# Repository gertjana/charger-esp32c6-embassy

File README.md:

# ESP32-C6 Embassy Charged

An ESP32-C6 based electric vehicle charging station built with Embassy async runtime and OCPP 1.6 support.

## Quick Start

### 1. Configuration Setup

Copy the example configuration file and update it with your settings:

```bash
cp app_config.toml.example app_config.toml
```

Edit `app_config.toml` with your actual values:

```toml
[wifi]
ssid = "YOUR_WIFI_NETWORK"
password = "YOUR_WIFI_PASSWORD"

[charger]
name = "esp32c6 charger 001"
model = "ESP32-C6"
vendor = "GA Make"
serial = "esp32c6-charger-001"

[mqtt]
broker = "broker.hivemq.com"
port = 1883
client_id = "esp32c6-charger-001"
```

### 2. Environment Variable Overrides (Optional)

You can override any configuration value using environment variables, the naming i:

```
CHARGER_<section>_key>
for instance CHARGER_WIFI_ID
```

### 3. Build and Flash

```bash
cargo build
cargo run
```

## OCPP Protocol Support

The charger implements OCPP 1.6 protocol:

### Outgoing Messages (Published to `/charger/{serial}`)
- **Authorize**: Sent when a user swipes their card for authorization
- **BootNotification**: Sent once at startup with charger model, vendor and serial details
- **Heartbeat**: Periodic status updates with configurable interval
- **StartTransaction**: Charging session initiation with ID tag and timestamp
- **StopTransaction**: Charging session completion with transaction ID and timestamp

### Responses and incoming Messages (Subscribed to `/system/{serial}`)

## Development

This project uses:
- **Embassy**: Async runtime for embedded Rust with concurrent task management
- **ESP-HAL**: Hardware abstraction for ESP32-C6
- **OCPP-RS**: Open Charge Point Protocol implementation
- **Embassy-Net**: Networking stack with WiFi and MQTT support
- **Rust-MQTT**: Lightweight MQTT client for embedded systems

### Architecture
The system is built around Embassy async tasks:
- **Network Stack**: WiFi connection management and IP configuration
- **MQTT Client**: Bidirectional message of OCPP Messages
- **NTP Client**: Queries NTP Server every 4 hours and syncing with local timer in the ESP32-C6
- **OCPP 1.6**: minimum support for OCPP 1.6 to support basic Charging behaviour
- **Hardware Tasks**: GPIO monitoring for cable detection, card swipes. Led and Relay control and update a small display
- **Periodic Tasks**: for instance Heartbeat transmission and boot notifications (once)

#### Application Diagram

#### State Diagram

### Memory Management
- **Heap Size**: 64KB allocated for dynamic memory
- **Message Buffers**: 2048-byte capacity for larger OCPP messages
- **Channel Queues**: 5-message capacity for MQTT send/receive operations
- **Static Allocation**: Embassy static cells for zero-allocation async runtime

## Security Note

The `app_config.toml` file contains sensitive information (WiFi passwords, etc.) and is excluded from version control. Always use the `.example` file as a template for new deployments.

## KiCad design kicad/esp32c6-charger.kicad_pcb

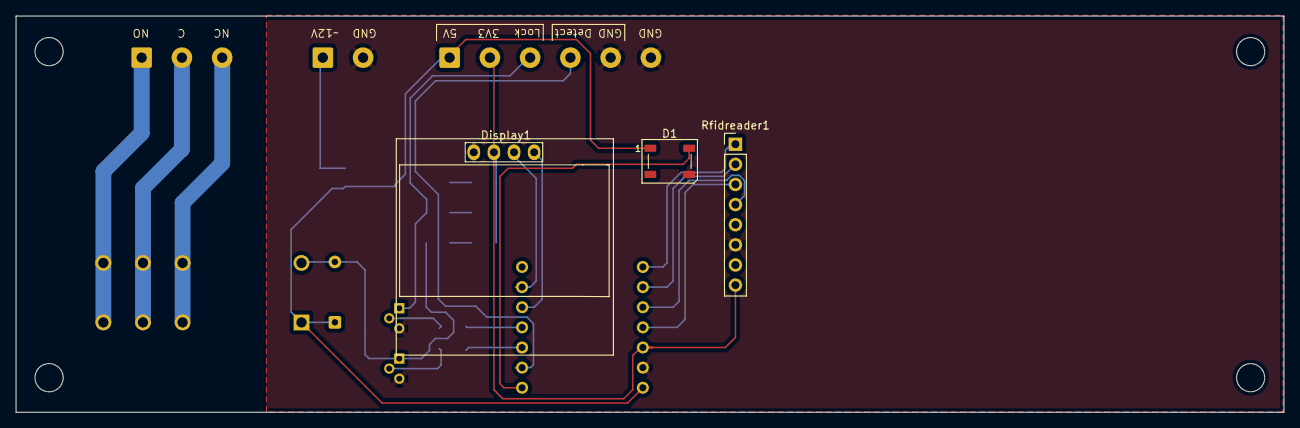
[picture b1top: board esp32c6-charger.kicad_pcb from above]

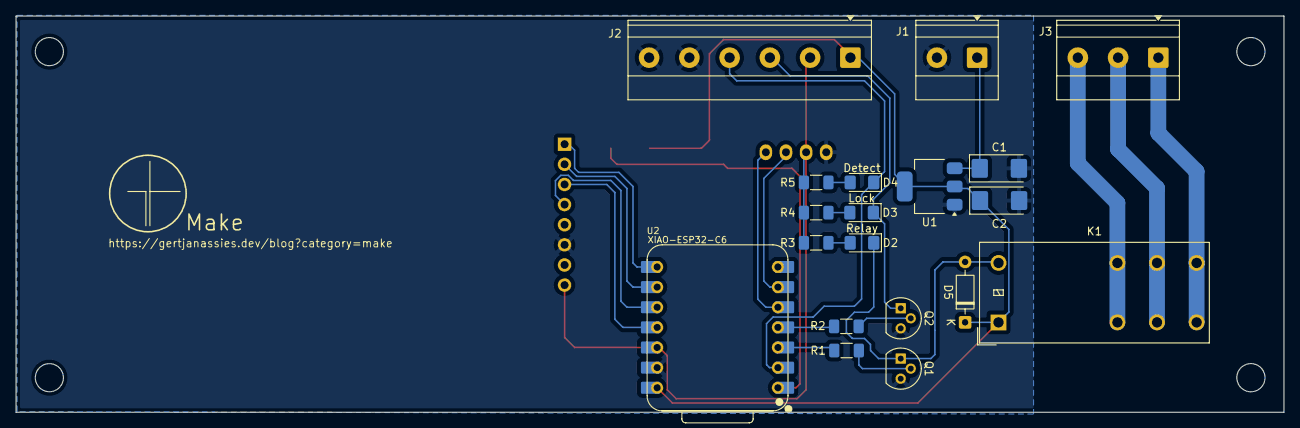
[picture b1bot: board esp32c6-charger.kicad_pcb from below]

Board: 2 copper layers, 160.0 x 50.0 mm, 22 parts (19 on the bottom side), 24 nets.

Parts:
C1: 10uF; CP_EIA-6032-28_Kemet-C
C2: 22uF; CP_EIA-6032-28_Kemet-C
D1: WS2812B; LED_WS2812B_PLCC4_5.0x5.0mm_P3.2mm
D2: Relay; LED_1206_3216Metric_Pad1.42x1.75mm_HandSolder
D3: Lock; LED_1206_3216Metric_Pad1.42x1.75mm_HandSolder
D4: Detect; LED_1206_3216Metric_Pad1.42x1.75mm_HandSolder
D5: 1N4148WS; D_DO-35_SOD27_P7.62mm_Horizontal
Display1: SSD1306; 128x64OLED
J1: Conn_01x02_Socket; TerminalBlock_Phoenix_MKDS-1,5-2-5.08_1x02_P5.08mm_Horizont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
J2: Power/Lock/Detect; TerminalBlock_Phoenix_MKDS-1,5-6-5.08_1x06_P5.08mm_Horizont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
J3: Relay; TerminalBlock_Phoenix_MKDS-1,5-3-5.08_1x03_P5.08mm_Horizont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
K1: G2RL-1; Relay_SPDT_Omron_G2RL-1-E
Q1, Q2: BC337; TO-92
R1, R2: 10k; R_1206_3216Metric_Pad1.30x1.75mm_HandSolder
R3, R4, R5: 68Ω; R_1206_3216Metric_Pad1.30x1.75mm_HandSolder
Rfidreader1: RC522
U1: AMS1117-5.0; SOT-223-3_TabPin2
U2: XIAO-ESP32-C6; XIAO-ESP32C6-DIP

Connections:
+12V: C1.1, J1.1, U1.3 (VI)
/CS: Rfidreader1.1 (SDA), U2.8 (GPIO17/D7/RX)
/Detect: D4.1 (K), J2.4, U2.2 (GPIO1/A1/D1)
/LED: D1.4 (DIN), U2.1 (GPIO0/A0/D0)
/Lock: D3.1 (K), J2.3, Q2.1 (C)
/MISO: Rfidreader1.4 (MISO), U2.10 (GPIO20/D9/MISO)
/MOSI: Rfidreader1.3 (MOSI), U2.11 (GPIO18/D10/MOSI)
/Relay: D2.1 (K), D5.2 (A), K1.A2, Q1.1 (C)
/SCK: Rfidreader1.2 (SCK), U2.9 (GPIO19/D8/SCK)
/SCL: Display1.3 (SCL), U2.6 (GPIO23/D5/SCL)
/SDA: Display1.4 (SDA), U2.5 (GPIO22/D4/SDA)
GND: C1.2, C2.2, D1.3 (VSS), Display1.1 (GND), J1.2, J2.5, J2.6, Q1.3 (E), Q2.3 (E), Rfidreader1.6 (GND), U1.1 (GND), U2.13 (GND)
unnamed: D2.2 (A), R3.1
unnamed: D3.2 (A), R4.1
unnamed: D4.2 (A), R5.1
unnamed: J3.1, K1.14
unnamed: J3.2, K1.11
unnamed: J3.3, K1.12
unnamed: Q1.2 (B), R1.2
unnamed: Q2.2 (B), R2.2
unnamed: R1.1, U2.3 (GPIO2/A2/D2)
unnamed: R2.1, U2.4 (GPIO21/D3)
VCC: Display1.2 (VCC), J2.2, R3.2, R4.2, R5.2, Rfidreader1.8 (3,3V), U2.12 (3V3)
VDD: C2.1, D1.1 (VDD), D5.1 (K), J2.1, K1.A1, U1.2 (VO), U2.14 (VBUS)

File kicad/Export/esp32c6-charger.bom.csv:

"Id";"Designator";"Footprint";"Quantity";"Designation";"Supplier and ref";
1;"Display1";"128x64OLED";1;"SSD1306";;;
2;"Rfidreader1";"RC522";1;"RC522";;;
3;"D1";"LED_WS2812B_PLCC4_5.0x5.0mm_P3.2mm";1;"WS2812B";;;
4;"U2";"XIAO-ESP32C6-DIP";1;"XIAO-ESP32-C6";;;
5;"D4";"LED_1206_3216Metric_Pad1.42x1.75mm_HandSolder";1;"Detect";;;
6;"D3";"LED_1206_3216Metric_Pad1.42x1.75mm_HandSolder";1;"Lock";;;
7;"R3,R4,R5";"R_1206_3216Metric_Pad1.30x1.75mm_HandSolder";3;"68Ω";;;
8;"D2";"LED_1206_3216Metric_Pad1.42x1.75mm_HandSolder";1;"Relay";;;
9;"Q2,Q1";"TO-92";2;"BC337";;;
10;"J1";"TerminalBlock_Phoenix_MKDS-1,5-2-5.08_1x02_P5.08mm_Horizontal";1;"Conn_01x02_Socket";;;
11;"C1";"CP_EIA-6032-28_Kemet-C";1;"10uF";;;
12;"R1,R2";"R_1206_3216Metric_Pad1.30x1.75mm_HandSolder";2;"10k";;;
13;"U1";"SOT-223-3_TabPin2";1;"AMS1117-5.0";;;
14;"K1";"Relay_SPDT_Omron_G2RL-1-E";1;"G2RL-1";;;
15;"J2";"TerminalBlock_Phoenix_MKDS-1,5-6-5.08_1x06_P5.08mm_Horizontal";1;"Power/Lock/Detect";;;
16;"J3";"TerminalBlock_Phoenix_MKDS-1,5-3-5.08_1x03_P5.08mm_Horizontal";1;"Relay";;;
17;"D5";"D_DO-35_SOD27_P7.62mm_Horizontal";1;"1N4148WS";;;
18;"C2";"CP_EIA-6032-28_Kemet-C";1;"22uF";;;

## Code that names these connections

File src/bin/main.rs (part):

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    let i2c = I2c::new(peripherals.I2C0, I2cConfig::default())
        .unwrap()
        .into_async()
        .with_sda(peripherals.GPIO22)
        .with_scl(peripherals.GPIO23);

    // Initialize SSD1306 display
    info!("MAIN: Initializing SSD1306 display...");
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        {
            let frequency = Rate::from_mhz(80);
            let rmt = Rmt::new(peripherals.RMT, frequency).expect("Failed to initialize RMT0");
            SmartLedsAdapter::new(rmt.channel0, peripherals.GPIO0, smart_led_buffer!(1))
        }
    );

    let cable_lock_pin = Output::new(peripherals.GPIO21, Level::Low, Default::default());

    let cable_switch = Input::new(
        peripherals.GPIO1,
        InputConfig::default().with_pull(Pull::Up),
    );

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                .with_mode(spi::Mode::_0),
        )
        .unwrap()
        .with_sck(peripherals.GPIO19)
        .with_mosi(peripherals.GPIO18)
        .with_miso(peripherals.GPIO20);
    // );

    let sd_cs = //mk_static!(Output,
        Output::new(peripherals.GPIO17, Level::High, OutputConfig::default());
    // );

    let charger_relay = Output::new(peripherals.GPIO2, Level::Low, Default::default());

    let charger = mk_static!(Charger, Charger::new());

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
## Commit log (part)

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2025-07-21 basic setup for an embassy project with wifi workingt and a blinking led
2025-07-21 basic github action
2025-07-25 Wired up the charger with tasks to handle it, got basic MQTT Sending working
2025-07-26 Pleasing the linting gods, or in this case fmt and clippy
2025-07-27 Added Dns Resolving and found a ocpp and a json crate that works with no_std, and implemented a heartbeat functionality
2025-07-27 Added Config file for all the 'configurables' added thread safe incrementing id for ocpp messages
2025-07-27 clippy
2025-07-27 Copy config to make sure app builds
2025-07-28 feat: Revamped the MQTT Section to use Embassy Channels to avoid deadlocks and implemented Heartbeat and BootNotification Messages
2025-07-28 Simple page to list todo's and bugs
2025-07-28 Had copilot draw up a best behaviour document based on the needs of this project
2025-07-28 Now we use a channel, the mutex is no longer necessary
2025-07-30 feat: Now support receiving of mqtt messages, fixed buffer sizes to accomodate larger mqtt messages. now using charger serial in the mqtt topics
2025-07-30 small update too reduce running on tools a bit
2025-07-30 Fixed co-pilot review's comment
2025-07-30 Updated configuration and Readme
2025-07-30 more config updates
2025-07-31 trimmed guidelines a bit
2025-07-31 Added custom NTP Client as there was no no_std version that I could find, also made the startup sequence wifi, wait, ntp, wait, mqtt
2025-07-31 now uses the local times to calculate the offset from the last ntp sync to keep the date/time current (the timer drift a couple of minutes a day
2025-08-01 Added d2 architecture diagram
2025-08-02 changed to png, as svg does not pick up the local paths to the icons
2025-08-02 without sketch looks better
2025-08-03 Added SSD1306 I2C Display showing serial, ip, state and time
2025-08-04 Copilot review comments
2025-08-04 Added simple TimeZone support
2025-08-04 Added a line
2025-08-04 fixed up some merge conflicts
2025-08-05 Added config for hearbeat interval and added a diagram for the state machine
2025-08-05 added esp32 image and some small updates
2025-08-05 Transition function already in state_diagram
2025-08-05 updated icons and function
2025-08-05 updated Readme (added state diagram)
2025-08-06 Got Avail -> Occupied -> Authorizing -> Charging flow working
2025-08-06 added line about logging with variables
2025-08-06 updated diagram and added script to generate png's from any d2 diagram found
2025-08-06 updated Readme and ToDo documents
2025-08-07 re-organised architecture folder, made script + GH Action to generate the diagrams
2025-08-07 added generated diagrams as they are used in the readme
2025-08-07 not use deprecated versions
2025-08-07 D2 is not an apt package
2025-08-07 Naming the GH Action
2025-08-07 Implemented some of CoPilot's review suggestions
2025-08-07 now shows all states, input- and outputevents
2025-08-07 Added cable lock handler and made all gpio input tasks more resistent to bouncing
2025-08-08 Updated TODO
2025-08-08 Refactored Debouncing into util function
2025-08-08 only run the generate diagrams pipeline when diagrams have changed
2025-08-08 State is now displayed more prominent on the display
2025-08-09 reverted debounce mechanism to a time delay again, works better
2025-08-09 Implemented Start and Stop Transaction Messages
2025-08-10 hopefully fixed bug with transaction_id
2025-08-10 pleasing the linting gods
2025-08-11 Restored the transaction_handler from the original branch as AI made a mess of it
2025-08-11 Updated diagrams
2025-08-11 Hardcoded id_tag is now in the configuration
2025-08-12 updated diagram
2025-08-12 Json parsing of strings that contains abritraty json, is not possible in a no_std env, string parsing it is
2025-08-13 Clean up logs and made it more specific
2025-08-13 also network stack logs are more consistent
2025-08-13 implemented rfid_reader for id_tag
2025-08-14 AI attempt at TLS
2025-08-14 added start of kicad schematic/pcb
2025-08-14 moved ai_guidelines.md to standard .github/copilot-instructions.md
2025-08-15 some improved in the ntp part
2025-08-15 Unknown transitions are now ignored
2025-08-15 fixed some comments
2025-08-15 Included Start/Stop Transactions in the Statemachine as the Backoffice can also Accept or Reject Transactions
2025-08-15 added pre-commit hooks
2025-08-15 updated diagrams, state now included Start/Stop transaction, Occupied is now Preparing
2025-08-15 Occupied is now Preparing
2025-08-15 running pre-commit fixed some things
2025-08-20 moved some of the configuration to it's own file
2025-08-20 added some pictures
2025-08-20 ignoring bunch of kicad files
2025-08-20 small updates to schema and pcb
2025-08-21 small updates to schema and pcbç√çç
2025-08-21 added external power possibility
2025-08-23 Remove reference instruction from guidelines
2025-08-24 updated changes to schematic and pcb
2025-08-24 small changes and a pdf of the schematic in the export jobset
2025-08-24 cleaned up Export Jobset
2025-08-24 Attempt to implement TLS for the MQTT Connection, keeping for prosperity
2025-08-29 updated 3d model for relay
2025-09-02 small changes to copper
2025-09-08 Latest exports of all pcb artifacts
2025-09-08 removed gerber zip
2025-09-08 small changes to diagram
2025-09-13 Got the WS2818B Led working
2025-09-13 updated 3d printable case
2025-09-13 moved local reference to smart-leds to a github one
2025-09-13 used normal transistors and diodes instead of SMD ones, we have the space, why make soldering life more difficult
2025-09-20 THT Transistors instead of SMT, export jobs now include solder masks and automatically zips them up
2025-09-20 clippy suggestions
2025-10-10 Small updates
2025-10-10 Moved all mqtt related functions from network.rs to mqtt.rs
2025-10-10 Now reverts back to Preparing State if the Authorizing state does not get a timely respond from the backend
2026-05-19 some small improvements
2026-05-20 consolidated on rust v1.90
2026-05-20 Implemented Accept/Reject for Transactions, starts charging, then stops when StartTransaction is rejected
2026-05-20 To be explicit also added the TxAccepted case, where nothing needs to happen
2026-05-20 removed commented out code, which was invalid anyways
